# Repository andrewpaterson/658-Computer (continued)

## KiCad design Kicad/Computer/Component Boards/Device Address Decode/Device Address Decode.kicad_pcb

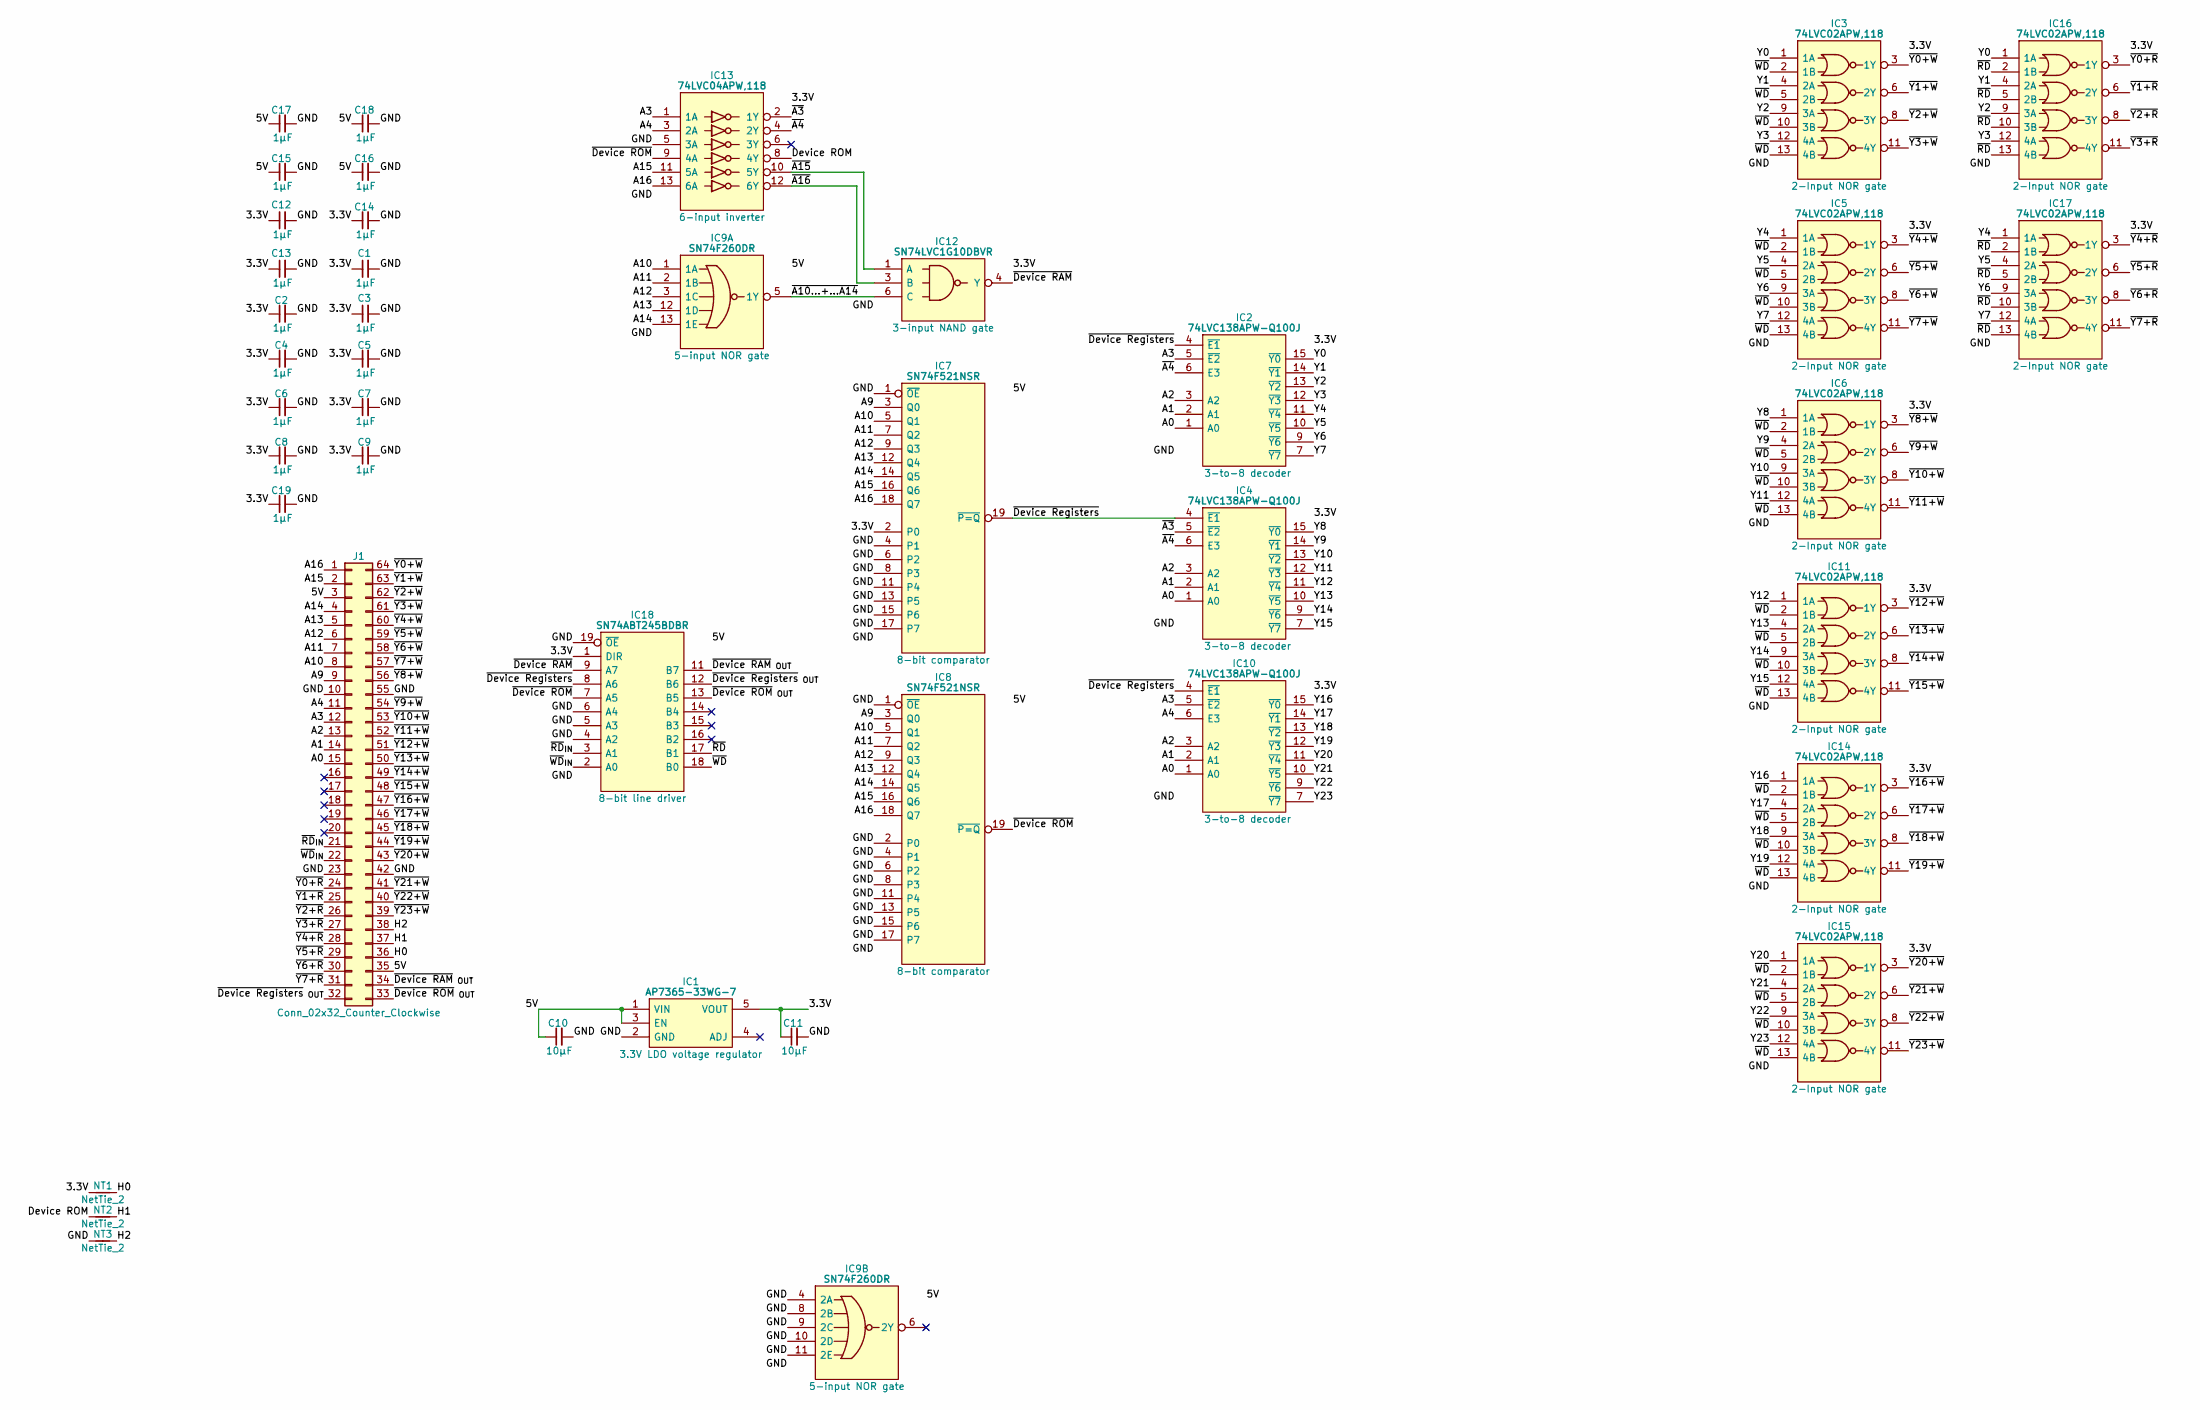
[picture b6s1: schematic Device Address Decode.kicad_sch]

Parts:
C1, C2, C3, C4, C5, C6, C7, C8, C9, C12, C13, C14, C15, C16, C17, C18, C19: 1μF; C_0805
C10, C11: 10µF; C_0805
IC1: AP7365-33WG-7; SOT95P285X130-5N; Manufacturer_Part_Number AP7365-33WG-7; Mouser Part Number 621-AP7365-33WG-7
IC2, IC4, IC10: 74LVC138APW-Q100J; SOP65P640X110-16N; Mouser Part Number 771-74LVC138APWQ100J
IC3, IC5, IC6, IC11, IC14, IC15, IC16, IC17: 74LVC02APW,118; SOP65P640X110-14N; Mouser Part Number 771-74LVC02APW-T
IC7, IC8: SN74F521NSR; SOIC127P780X200-20N; Mouser Part Number 595-SN74F521NSR
IC9: SN74F260DR; SOIC127P600X175-14N; Manufacturer_Part_Number SN74F260DR; Mouser Part Number 595-SN74F260DR
IC12: SN74LVC1G10DBVR; SOT95P280X145-6N; Manufacturer_Part_Number SN74LVC1G10DBVR; Mouser Part Number 595-SN74LVC1G10DBVR
IC13: 74LVC04APW,118; SOP65P640X110-14N; Manufacturer_Part_Number 74LVC04APW,118; Mouser Part Number 771-74LVC04APW-T
IC18: SN74ABT245BDBR; SOP65P780X200-20N; Manufacturer_Part_Number SN74ABT245BDBR; Mouser Part Number 595-SN74ABT245BDBR
J1: Conn_02x32_Counter_Clockwise; DIP-64_Board_W22.86mm
NT1, NT2, NT3: NetTie_2; NetTie-2_SMD_Pad0.5mm

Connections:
/3.3V: C1.1, C2.1, C3.1, C4.1, C5.1, C6.1, C7.1, C8.1, C9.1, C11.1, C12.1, C13.1, C14.1, C19.1, IC1.5 (VOUT), IC2.16 (3V), IC3.14 (3V), IC4.16 (3V), IC5.14 (3V), IC6.14 (3V), IC7.2 (P0), IC10.16 (3V), IC11.14 (3V), IC12.5 (3V), IC13.14 (3V), IC14.14 (3V), IC15.14 (3V), IC16.14 (3V), IC17.14 (3V), IC18.1 (DIR), NT1.1
/5V: C10.1, C15.1, C16.1, C17.1, C18.1, IC1.1 (VIN), IC1.3 (EN), IC7.20 (5V), IC8.20 (5V), IC9.14 (5V), IC18.20 (5V), J1.3, J1.35
/A0: IC2.1 (A0), IC4.1 (A0), IC10.1 (A0), J1.15
/A1: IC2.2 (A1), IC4.2 (A1), IC10.2 (A1), J1.14
/A2: IC2.3 (A2), IC4.3 (A2), IC10.3 (A2), J1.13
/A3: IC2.5 (~E2), IC10.5 (~E2), IC13.1 (1A), J1.12
/A4: IC10.6 (E3), IC13.3 (2A), J1.11
/A9: IC7.3 (Q0), IC8.3 (Q0), J1.9
/A10: IC7.5 (Q1), IC8.5 (Q1), IC9.1 (1A), J1.8
/A11: IC7.7 (Q2), IC8.7 (Q2), IC9.2 (1B), J1.7
/A12: IC7.9 (Q3), IC8.9 (Q3), IC9.3 (1C), J1.6
/A13: IC7.12 (Q4), IC8.12 (Q4), IC9.12 (1D), J1.5
/A14: IC7.14 (Q5), IC8.14 (Q5), IC9.13 (1E), J1.4
/A15: IC7.16 (Q6), IC8.16 (Q6), IC13.11 (5A), J1.2
/A16: IC7.18 (Q7), IC8.18 (Q7), IC13.13 (6A), J1.1
/Device ROM: IC13.8 (4Y), NT2.1
/GND: C1.2, C2.2, C3.2, C4.2, C5.2, C6.2, C7.2, C8.2, C9.2, C10.2, C11.2, C12.2, C13.2, C14.2, C15.2, C16.2, C17.2, C18.2, C19.2, IC1.2 (GND), IC2.8 (GND), IC3.7 (GND), IC4.8 (GND), IC5.7 (GND), IC6.7 (GND), IC7.1 (~OE), IC7.4 (P1), IC7.6 (P2), IC7.8 (P3), IC7.10 (GND), IC7.11 (P4), IC7.13 (P5), IC7.15 (P6), IC7.17 (P7), IC8.1 (~OE), IC8.2 (P0), IC8.4 (P1), IC8.6 (P2), IC8.8 (P3), IC8.10 (GND), IC8.11 (P4), IC8.13 (P5), IC8.15 (P6), IC8.17 (P7), IC9.4 (2A), IC9.7 (GND), IC9.8 (2B), IC9.9 (2C), IC9.10 (2D), IC9.11 (2E), IC10.8 (GND), IC11.7 (GND), IC12.2 (GND), IC13.5 (3A), IC13.7 (GND), IC14.7 (GND), IC15.7 (GND), IC16.7 (GND), IC17.7 (GND), IC18.4 (A2), IC18.5 (A3), IC18.6 (A4), IC18.10 (GND), IC18.19 (~OE), J1.10, J1.23, J1.42, J1.55, NT3.1
/H0: J1.36, NT1.2
/H1: J1.37, NT2.2
/H2: J1.38, NT3.2
/Y0: IC2.15 (~Y0), IC3.1 (1A), IC16.1 (1A)
/Y1: IC2.14 (~Y1), IC3.4 (2A), IC16.4 (2A)
/Y2: IC2.13 (~Y2), IC3.9 (3A), IC16.9 (3A)
/Y3: IC2.12 (~Y3), IC3.12 (4A), IC16.12 (4A)
/Y4: IC2.11 (~Y4), IC5.1 (1A), IC17.1 (1A)
/Y5: IC2.10 (~Y5), IC5.4 (2A), IC17.4 (2A)
/Y6: IC2.9 (~Y6), IC5.9 (3A), IC17.9 (3A)
/Y7: IC2.7 (~Y7), IC5.12 (4A), IC17.12 (4A)
/Y8: IC4.15 (~Y0), IC6.1 (1A)
/Y9: IC4.14 (~Y1), IC6.4 (2A)
/Y10: IC4.13 (~Y2), IC6.9 (3A)
/Y11: IC4.12 (~Y3), IC6.12 (4A)
/Y12: IC4.11 (~Y4), IC11.1 (1A)
/Y13: IC4.10 (~Y5), IC11.4 (2A)
/Y14: IC4.9 (~Y6), IC11.9 (3A)
/Y15: IC4.7 (~Y7), IC11.12 (4A)
/Y16: IC10.15 (~Y0), IC14.1 (1A)
/Y17: IC10.14 (~Y1), IC14.4 (2A)
/Y18: IC10.13 (~Y2), IC14.9 (3A)
/Y19: IC10.12 (~Y3), IC14.12 (4A)
/Y20: IC10.11 (~Y4), IC15.1 (1A)
/Y21: IC10.10 (~Y5), IC15.4 (2A)
/Y22: IC10.9 (~Y6), IC15.9 (3A)
/Y23: IC10.7 (~Y7), IC15.12 (4A)
/~A3: IC4.5 (~E2), IC13.2 (1Y)
/~A4: IC2.6 (E3), IC4.6 (E3), IC13.4 (2Y)
/~A10...+...A14: IC9.5 (1Y), IC12.6 (C)
/~A15: IC12.1 (A), IC13.10 (5Y)
/~A16: IC12.3 (B), IC13.12 (6Y)
/~Device RAM: IC12.4 (Y), IC18.9 (A7)
/~Device RAM_{ OUT}: IC18.11 (B7), J1.34
/~Device ROM: IC8.19 (~P=Q), IC13.9 (4A), IC18.7 (A5)
/~Device ROM_{ OUT}: IC18.13 (B5), J1.33
/~Device Registers: IC2.4 (~E1), IC4.4 (~E1), IC7.19 (~P=Q), IC10.4 (~E1), IC18.8 (A6)
/~Device Registers_{ OUT}: IC18.12 (B6), J1.32
/~RD: IC16.2 (1B), IC16.5 (2B), IC16.10 (3B), IC16.13 (4B), IC17.2 (1B), IC17.5 (2B), IC17.10 (3B), IC17.13 (4B), IC18.17 (B1)
/~RD_{IN}: IC18.3 (A1), J1.21
/~WD: IC3.2 (1B), IC3.5 (2B), IC3.10 (3B), IC3.13 (4B), IC5.2 (1B), IC5.5 (2B), IC5.10 (3B), IC5.13 (4B), IC6.2 (1B), IC6.5 (2B), IC6.10 (3B), IC6.13 (4B), IC11.2 (1B), IC11.5 (2B), IC11.10 (3B), IC11.13 (4B), IC14.2 (1B), IC14.5 (2B), IC14.10 (3B), IC14.13 (4B), IC15.2 (1B), IC15.5 (2B), IC15.10 (3B), IC15.13 (4B), IC18.18 (B0)
/~WD_{IN}: IC18.2 (A0), J1.22
/~Y0+R: IC16.3 (1Y), J1.24
/~Y0+W: IC3.3 (1Y), J1.64
/~Y1+R: IC16.6 (2Y), J1.25
/~Y1+W: IC3.6 (2Y), J1.63
/~Y2+R: IC16.8 (3Y), J1.26
/~Y2+W: IC3.8 (3Y), J1.62
/~Y3+R: IC16.11 (4Y), J1.27
/~Y3+W: IC3.11 (4Y), J1.61
/~Y4+R: IC17.3 (1Y), J1.28
/~Y4+W: IC5.3 (1Y), J1.60
/~Y5+R: IC17.6 (2Y), J1.29
/~Y5+W: IC5.6 (2Y), J1.59
/~Y6+R: IC17.8 (3Y), J1.30
/~Y6+W: IC5.8 (3Y), J1.58
/~Y7+R: IC17.11 (4Y), J1.31
/~Y7+W: IC5.11 (4Y), J1.57
/~Y8+W: IC6.3 (1Y), J1.56
/~Y9+W: IC6.6 (2Y), J1.54
/~Y10+W: IC6.8 (3Y), J1.53
/~Y11+W: IC6.11 (4Y), J1.52
/~Y12+W: IC11.3 (1Y), J1.51
/~Y13+W: IC11.6 (2Y), J1.50
/~Y14+W: IC11.8 (3Y), J1.49
/~Y15+W: IC11.11 (4Y), J1.48
/~Y16+W: IC14.3 (1Y), J1.47
/~Y17+W: IC14.6 (2Y), J1.46
/~Y18+W: IC14.8 (3Y), J1.45
/~Y19+W: IC14.11 (4Y), J1.44
/~Y20+W: IC15.3 (1Y), J1.43
/~Y21+W: IC15.6 (2Y), J1.41
/~Y22+W: IC15.8 (3Y), J1.40
/~Y23+W: IC15.11 (4Y), J1.39

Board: 2 copper layers, 41 parts (0 on the bottom side), 91 nets, no tracks yet.

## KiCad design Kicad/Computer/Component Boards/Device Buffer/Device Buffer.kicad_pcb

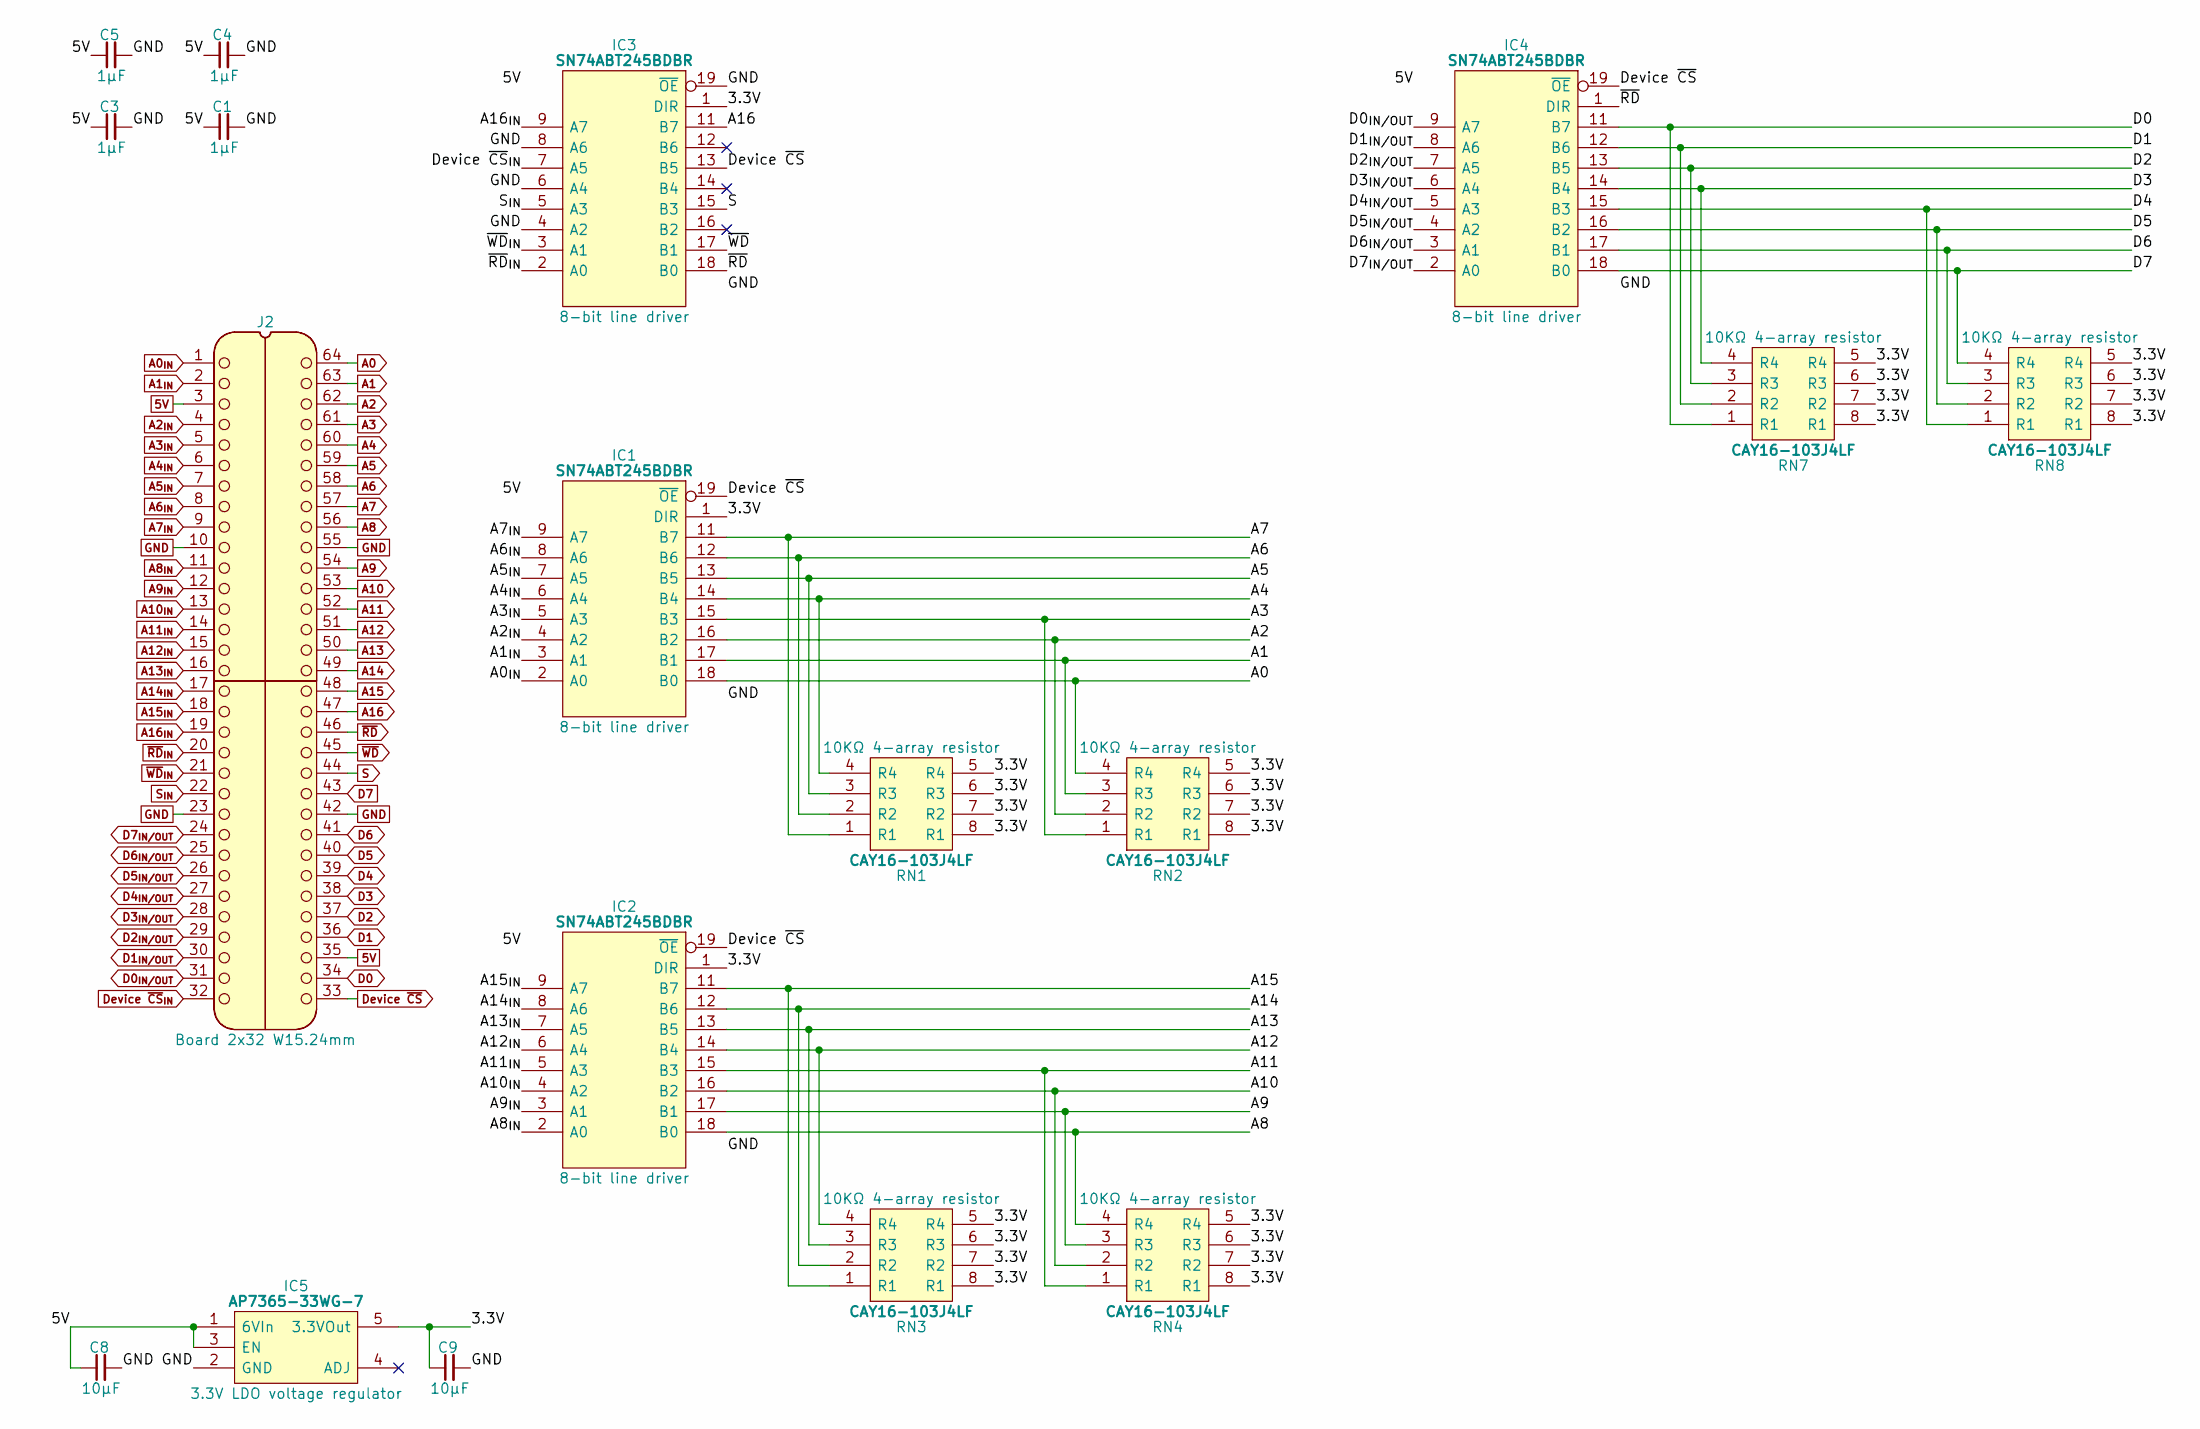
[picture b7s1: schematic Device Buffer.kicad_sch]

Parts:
C1, C3, C4, C5: 1μF; C_0805
C8, C9: 10µF; C_0805
IC1, IC2, IC3, IC4: SN74ABT245BDBR; SOP65P780X200-20N; Manufacturer_Part_Number SN74ABT245BDBR; Mouser Part Number 595-SN74ABT245BDBR
IC5: AP7365-33WG-7; SOT95P285X130-5N; Manufacturer_Part_Number AP7365-33WG-7; Mouser Part Number 621-AP7365-33WG-7
J2: Board 2x32 W15.24mm; DIP-64_Board_W15.24mm
RN1, RN2, RN3, RN4, RN7, RN8: CAY16-103J4LF; CAY16-J4; Manufacturer_Part_Number CAY16-103J4LF; Mouser Part Number 652-CAY16-103J4LF

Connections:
5V: C1.1, C3.1, C4.1, C5.1, C8.1, IC1.20 (5V), IC2.20 (5V), IC3.20 (5V), IC4.20 (5V), IC5.1 (6VIn), IC5.3 (EN), J2.3, J2.35
/3.3V: C9.1, IC1.1 (DIR), IC2.1 (DIR), IC3.1 (DIR), IC5.5 (3.3VOut), RN1.5 (R4), RN1.6 (R3), RN1.7 (R2), RN1.8 (R1), RN2.5 (R4), RN2.6 (R3), RN2.7 (R2), RN2.8 (R1), RN3.5 (R4), RN3.6 (R3), RN3.7 (R2), RN3.8 (R1), RN4.5 (R4), RN4.6 (R3), RN4.7 (R2), RN4.8 (R1), RN7.5 (R4), RN7.6 (R3), RN7.7 (R2), RN7.8 (R1), RN8.5 (R4), RN8.6 (R3), RN8.7 (R2), RN8.8 (R1)
A0: IC1.18 (B0), J2.64, RN2.4 (R4)
A0_{IN}: IC1.2 (A0), J2.1
A1: IC1.17 (B1), J2.63, RN2.3 (R3)
A1_{IN}: IC1.3 (A1), J2.2
A2: IC1.16 (B2), J2.62, RN2.2 (R2)
A2_{IN}: IC1.4 (A2), J2.4
A3: IC1.15 (B3), J2.61, RN2.1 (R1)
A3_{IN}: IC1.5 (A3), J2.5
A4: IC1.14 (B4), J2.60, RN1.4 (R4)
A4_{IN}: IC1.6 (A4), J2.6
A5: IC1.13 (B5), J2.59, RN1.3 (R3)
A5_{IN}: IC1.7 (A5), J2.7
A6: IC1.12 (B6), J2.58, RN1.2 (R2)
A6_{IN}: IC1.8 (A6), J2.8
A7: IC1.11 (B7), J2.57, RN1.1 (R1)
A7_{IN}: IC1.9 (A7), J2.9
A8: IC2.18 (B0), J2.56, RN4.4 (R4)
A8_{IN}: IC2.2 (A0), J2.11
A9: IC2.17 (B1), J2.54, RN4.3 (R3)
A9_{IN}: IC2.3 (A1), J2.12
A10: IC2.16 (B2), J2.53, RN4.2 (R2)
A10_{IN}: IC2.4 (A2), J2.13
A11: IC2.15 (B3), J2.52, RN4.1 (R1)
A11_{IN}: IC2.5 (A3), J2.14
A12: IC2.14 (B4), J2.51, RN3.4 (R4)
A12_{IN}: IC2.6 (A4), J2.15
A13: IC2.13 (B5), J2.50, RN3.3 (R3)
A13_{IN}: IC2.7 (A5), J2.16
A14: IC2.12 (B6), J2.49, RN3.2 (R2)
A14_{IN}: IC2.8 (A6), J2.17
A15: IC2.11 (B7), J2.48, RN3.1 (R1)
A15_{IN}: IC2.9 (A7), J2.18
A16: IC3.11 (B7), J2.47
A16_{IN}: IC3.9 (A7), J2.19
D0: IC4.11 (B7), J2.34, RN7.1 (R1)
D0_{IN/OUT}: IC4.9 (A7), J2.31
D1: IC4.12 (B6), J2.36, RN7.2 (R2)
D1_{IN/OUT}: IC4.8 (A6), J2.30
D2: IC4.13 (B5), J2.37, RN7.3 (R3)
D2_{IN/OUT}: IC4.7 (A5), J2.29
D3: IC4.14 (B4), J2.38, RN7.4 (R4)
D3_{IN/OUT}: IC4.6 (A4), J2.28
D4: IC4.15 (B3), J2.39, RN8.1 (R1)
D4_{IN/OUT}: IC4.5 (A3), J2.27
D5: IC4.16 (B2), J2.40, RN8.2 (R2)
D5_{IN/OUT}: IC4.4 (A2), J2.26
D6: IC4.17 (B1), J2.41, RN8.3 (R3)
D6_{IN/OUT}: IC4.3 (A1), J2.25
D7: IC4.18 (B0), J2.43, RN8.4 (R4)
D7_{IN/OUT}: IC4.2 (A0), J2.24
Device ~CS: IC1.19 (~OE), IC2.19 (~OE), IC3.13 (B5), IC4.19 (~OE), J2.33
Device ~CS_{IN}: IC3.7 (A5), J2.32
GND: C1.2, C3.2, C4.2, C5.2, C8.2, C9.2, IC1.10 (GND), IC2.10 (GND), IC3.4 (A2), IC3.6 (A4), IC3.8 (A6), IC3.10 (GND), IC3.19 (~OE), IC4.10 (GND), IC5.2 (GND), J2.10, J2.23, J2.42, J2.55
S: IC3.15 (B3), J2.44
S_{IN}: IC3.5 (A3), J2.22
~RD: IC3.18 (B0), IC4.1 (DIR), J2.46
~RD_{IN}: IC3.2 (A0), J2.20
~WD: IC3.17 (B1), J2.45
~WD_{IN}: IC3.3 (A1), J2.21

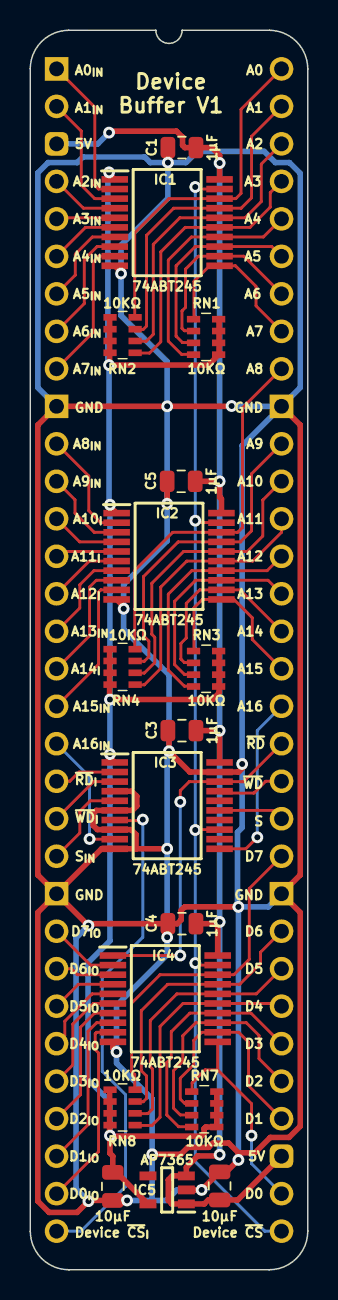
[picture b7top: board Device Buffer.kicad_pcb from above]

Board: 2 copper layers, 18.8 x 84.0 mm, 18 parts (0 on the bottom side), 61 nets.

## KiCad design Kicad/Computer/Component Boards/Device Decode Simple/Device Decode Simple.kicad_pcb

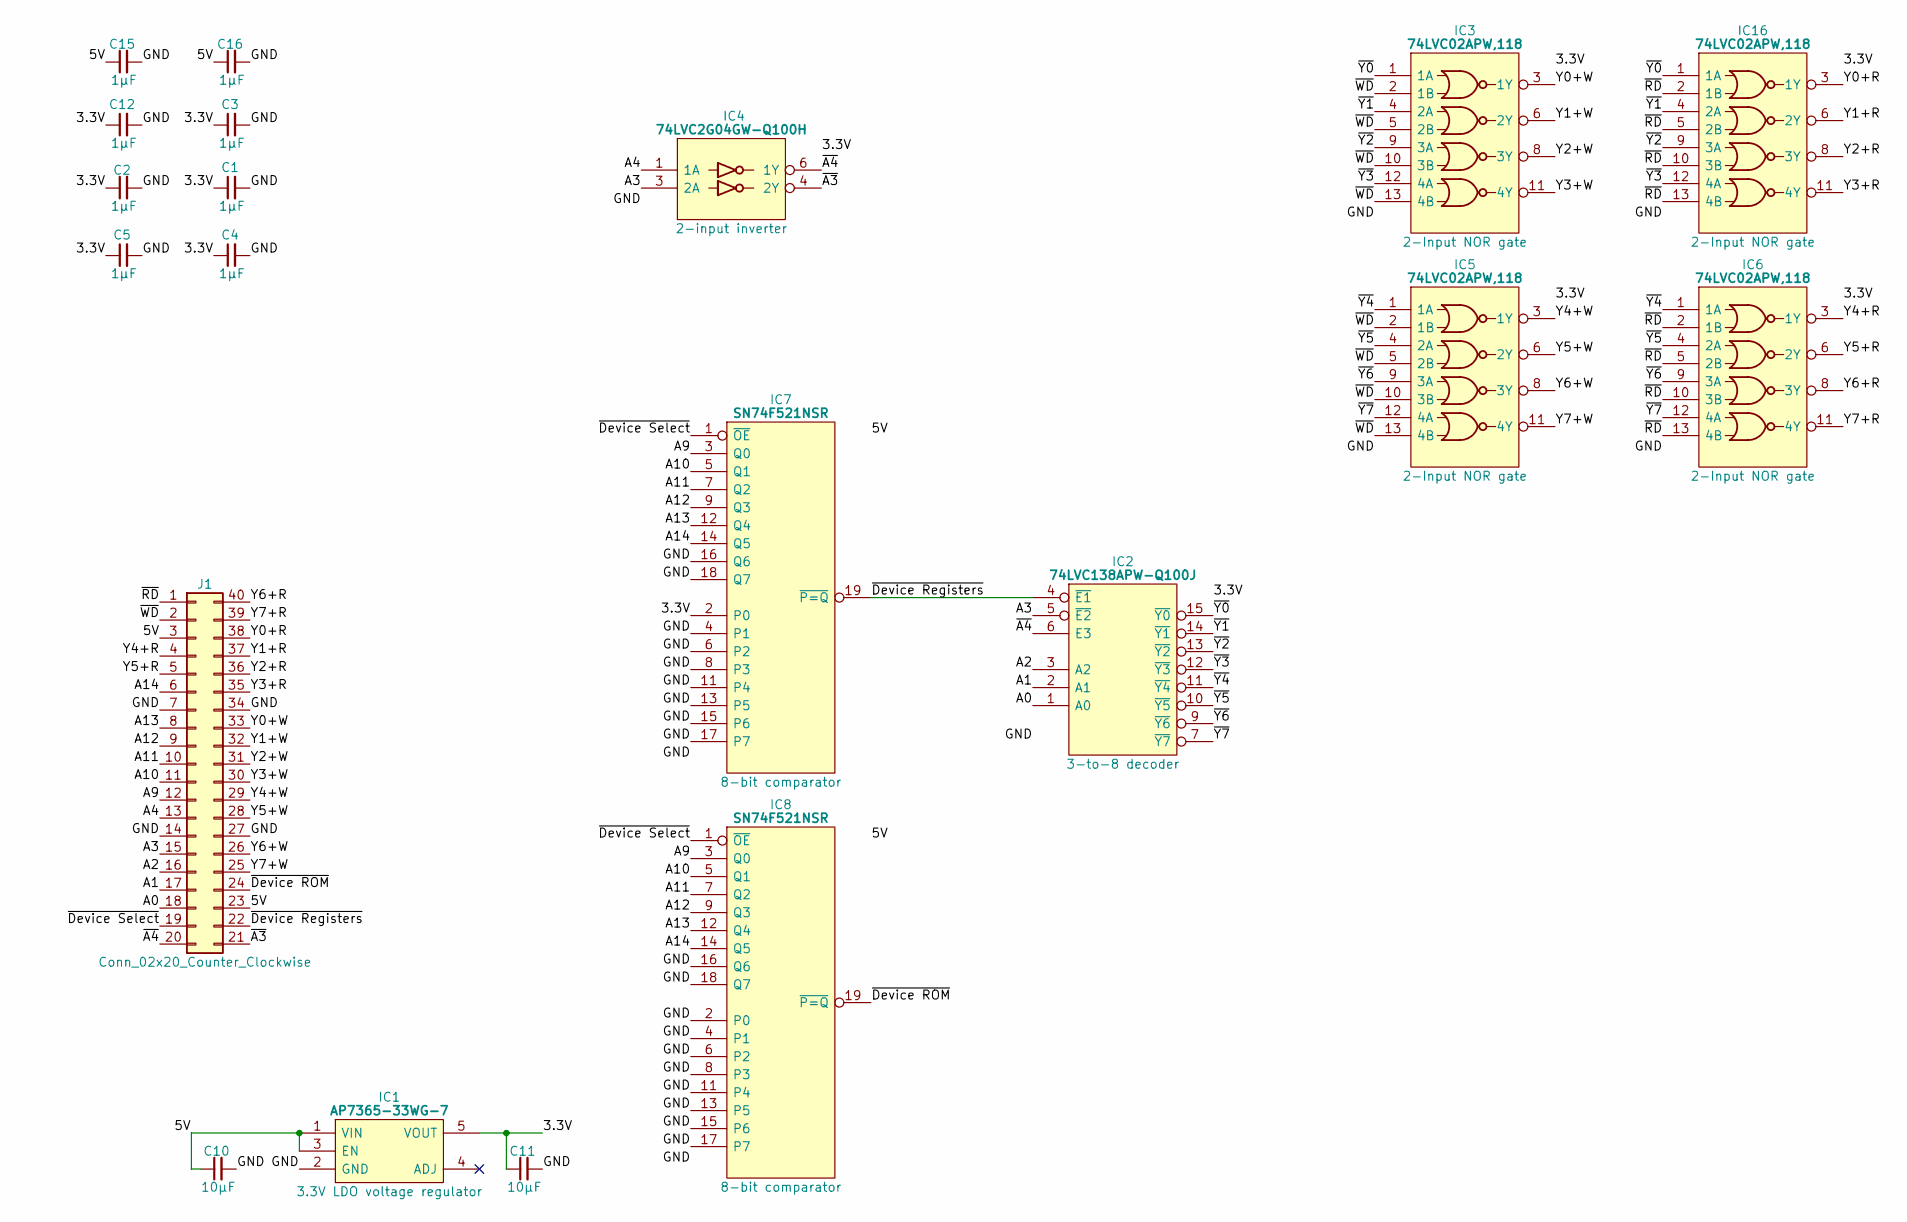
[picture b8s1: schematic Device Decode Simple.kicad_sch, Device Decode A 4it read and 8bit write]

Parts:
C1, C2, C3, C4, C5, C12, C15, C16: 1μF; C_0805
C10, C11: 10µF; C_0805
IC1: AP7365-33WG-7; SOT95P285X130-5N; Manufacturer_Part_Number AP7365-33WG-7; Mouser Part Number 621-AP7365-33WG-7
IC2: 74LVC138APW-Q100J; SOP65P640X110-16N; Mouser Part Number 771-74LVC138APWQ100J
IC3, IC5, IC6, IC16: 74LVC02APW,118; SOP65P640X110-14N; Mouser Part Number 771-74LVC02APW-T
IC4: 74LVC2G04GW-Q100H; SOP65P210X110-6N; Manufacturer_Part_Number 74LVC2G04GW-Q100H; Mouser Part Number 771-74LVC2G04GWQ100H
IC7, IC8: SN74F521NSR; SOIC127P780X200-20N; Mouser Part Number 595-SN74F521NSR
J1: Conn_02x20_Counter_Clockwise; DIP-40_Board_W22.86mm

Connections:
/3.3V: C1.1, C2.1, C3.1, C4.1, C5.1, C11.1, C12.1, IC1.5 (VOUT), IC2.16 (3V), IC3.14 (3V), IC4.5 (3V), IC5.14 (3V), IC6.14 (3V), IC7.2 (P0), IC16.14 (3V)
/5V: C10.1, C15.1, C16.1, IC1.1 (VIN), IC1.3 (EN), IC7.20 (5V), IC8.20 (5V), J1.3, J1.23
/A0: IC2.1 (A0), J1.18
/A1: IC2.2 (A1), J1.17
/A2: IC2.3 (A2), J1.16
/A3: IC2.5 (~E2), IC4.3 (2A), J1.15
/A4: IC4.1 (1A), J1.13
/A9: IC7.3 (Q0), IC8.3 (Q0), J1.12
/A10: IC7.5 (Q1), IC8.5 (Q1), J1.11
/A11: IC7.7 (Q2), IC8.7 (Q2), J1.10
/A12: IC7.9 (Q3), IC8.9 (Q3), J1.9
/A13: IC7.12 (Q4), IC8.12 (Q4), J1.8
/A14: IC7.14 (Q5), IC8.14 (Q5), J1.6
/GND: C1.2, C2.2, C3.2, C4.2, C5.2, C10.2, C11.2, C12.2, C15.2, C16.2, IC1.2 (GND), IC2.8 (GND), IC3.7 (GND), IC4.2 (GND), IC5.7 (GND), IC6.7 (GND), IC7.4 (P1), IC7.6 (P2), IC7.8 (P3), IC7.10 (GND), IC7.11 (P4), IC7.13 (P5), IC7.15 (P6), IC7.16 (Q6), IC7.17 (P7), IC7.18 (Q7), IC8.2 (P0), IC8.4 (P1), IC8.6 (P2), IC8.8 (P3), IC8.10 (GND), IC8.11 (P4), IC8.13 (P5), IC8.15 (P6), IC8.16 (Q6), IC8.17 (P7), IC8.18 (Q7), IC16.7 (GND), J1.7, J1.14, J1.27, J1.34
/Y0+R: IC16.3 (1Y), J1.38
/Y0+W: IC3.3 (1Y), J1.33
/Y1+R: IC16.6 (2Y), J1.37
/Y1+W: IC3.6 (2Y), J1.32
/Y2+R: IC16.8 (3Y), J1.36
/Y2+W: IC3.8 (3Y), J1.31
/Y3+R: IC16.11 (4Y), J1.35
/Y3+W: IC3.11 (4Y), J1.30
/Y4+R: IC6.3 (1Y), J1.4
/Y4+W: IC5.3 (1Y), J1.29
/Y5+R: IC6.6 (2Y), J1.5
/Y5+W: IC5.6 (2Y), J1.28
/Y6+R: IC6.8 (3Y), J1.40
/Y6+W: IC5.8 (3Y), J1.26
/Y7+R: IC6.11 (4Y), J1.39
/Y7+W: IC5.11 (4Y), J1.25
/~A3: IC4.4 (2Y), J1.21
/~A4: IC2.6 (E3), IC4.6 (1Y), J1.20
/~Device ROM: IC8.19 (~P=Q), J1.24
/~Device Registers: IC2.4 (~E1), IC7.19 (~P=Q), J1.22
/~Device Select: IC7.1 (~OE), IC8.1 (~OE), J1.19
/~RD: IC6.2 (1B), IC6.5 (2B), IC6.10 (3B), IC6.13 (4B), IC16.2 (1B), IC16.5 (2B), IC16.10 (3B), IC16.13 (4B), J1.1
/~WD: IC3.2 (1B), IC3.5 (2B), IC3.10 (3B), IC3.13 (4B), IC5.2 (1B), IC5.5 (2B), IC5.10 (3B), IC5.13 (4B), J1.2
/~Y0: IC2.15 (~Y0), IC3.1 (1A), IC16.1 (1A)
/~Y1: IC2.14 (~Y1), IC3.4 (2A), IC16.4 (2A)
/~Y2: IC2.13 (~Y2), IC3.9 (3A), IC16.9 (3A)
/~Y3: IC2.12 (~Y3), IC3.12 (4A), IC16.12 (4A)
/~Y4: IC2.11 (~Y4), IC5.1 (1A), IC6.1 (1A)
/~Y5: IC2.10 (~Y5), IC5.4 (2A), IC6.4 (2A)
/~Y6: IC2.9 (~Y6), IC5.9 (3A), IC6.9 (3A)
/~Y7: IC2.7 (~Y7), IC5.12 (4A), IC6.12 (4A)

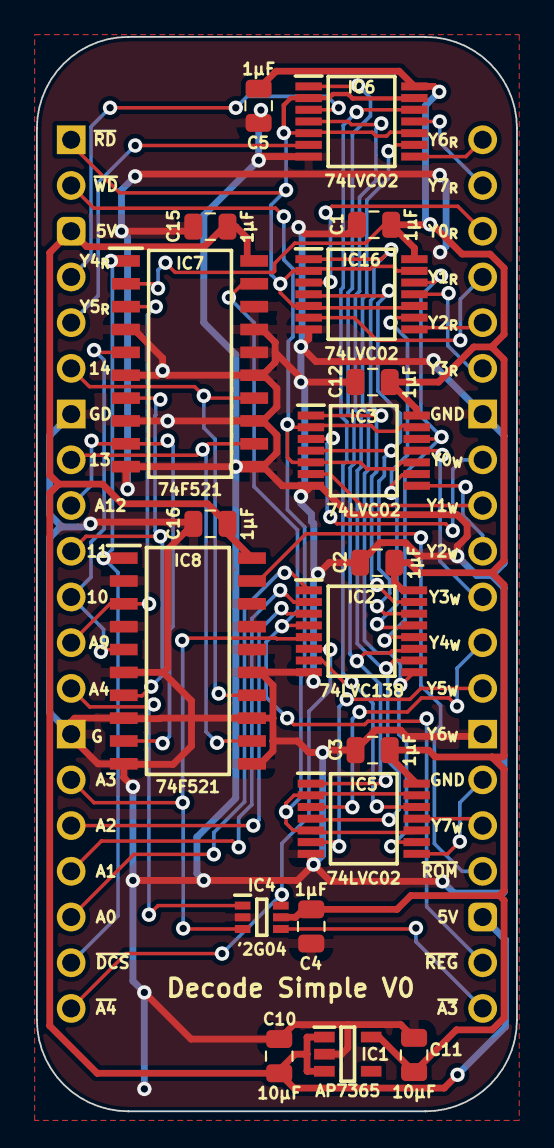
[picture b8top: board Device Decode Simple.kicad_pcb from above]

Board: 2 copper layers, 26.7 x 59.7 mm, 20 parts (0 on the bottom side), 45 nets.
